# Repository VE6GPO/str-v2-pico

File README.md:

# Controlling NJW1194 pre-amp with RasPi Pico or Arduino Nano

### NJW1194 has:
- 4 stereo inputs
- SPI interface
- Volume control (separate L/R)
- Tone controls (Bass/Treble)

## Requirements:

### Audio inputs:
- AM Radio
- FM Radio
- IP Radio (Raspberry Pi as an internet radio stream receiver)
- External input (TV)

### MCU inputs - total 12 GPI:
- Power switch - 1 GPI
- Phono/AM/FM switch - 3 GPI
- Tape Select - 1 GPI
- Volume (rotary ctrl) - 2 GPI
- Mute - 1 GPI
- Bass/Treble/Balance - 3 ADC
- IR receiver - 1 GPI

### MCU outputs - total 9 GPO:
- Power relay - 1 GPO
- SPI (Data, Clock, ChipSelect) - 3 GPO
- RGB dial light (PWM) - 3 GPO
- Display I2C - 2 GPO

MCU needs 21 GPIO lines in total, plus maybe another 2 to "talk" to Raspberry Pi ...

### TODO:

- Utilize rotary encoder w. push button for Volume/Mute control
- Use existing pots fed to ADC for controlling Tone + Balance

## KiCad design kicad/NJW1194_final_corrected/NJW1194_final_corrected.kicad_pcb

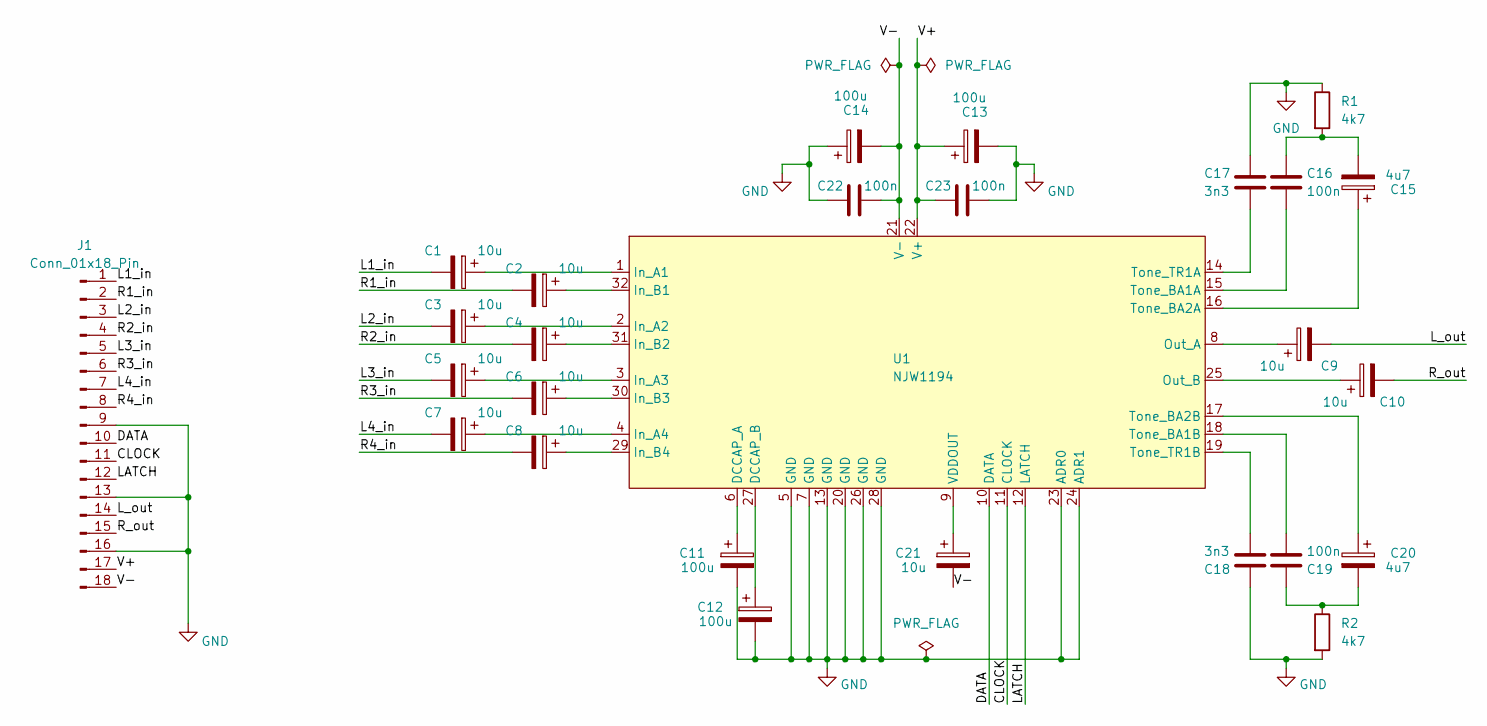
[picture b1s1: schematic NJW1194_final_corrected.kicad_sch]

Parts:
C1, C2, C3, C4, C5, C6, C7, C8, C9, C10, C21: 10u; CP_Elec_4x5.7
C11, C12, C13, C14: 100u; CP_Elec_6.3x7.7
C15, C20: 4u7; CP_Elec_4x5.7
C16, C19, C22, C23: 100n; C_0805_2012Metric_Pad1.18x1.45mm_HandSolder
C17, C18: 3n3; C_0805_2012Metric_Pad1.18x1.45mm_HandSolder
J1: Conn_01x18_Pin; PinHeader_1x18_P2.54mm_Vertical
R1, R2: 4k7; R_1206_3216Metric_Pad1.30x1.75mm_HandSolder
U1: NJW1194; TSSOP-32_6.1x11mm_P0.65mm

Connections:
/CLOCK: J1.11, U1.11 (CLOCK)
/DATA: J1.10, U1.10 (DATA)
/L1_in: C1.2, J1.1
/L2_in: C3.2, J1.3
/L3_in: C5.2, J1.5
/L4_in: C7.2, J1.7
/LATCH: J1.12, U1.12 (LATCH)
/L_out: C9.2, J1.14
/R1_in: C2.2, J1.2
/R2_in: C4.2, J1.4
/R3_in: C6.2, J1.6
/R4_in: C8.2, J1.8
/R_out: C10.2, J1.15
/V+: C13.1, C23.2, J1.17, U1.22 (V+)
/V-: C14.2, C21.2, C22.1, J1.18, U1.21 (V-)
GND: C11.2, C12.2, C13.2, C14.1, C17.1, C18.1, C22.2, C23.1, J1.9, J1.13, J1.16, R1.1, R2.2, U1.5 (GND), U1.7 (GND), U1.13 (GND), U1.20 (GND), U1.23 (ADR0), U1.24 (ADR1), U1.26 (GND), U1.28 (GND)
unnamed: C15.2, C16.1, R1.2
unnamed: C19.1, C20.2, R2.1
unnamed: C11.1, U1.6 (DCCAP_A)
unnamed: C12.1, U1.27 (DCCAP_B)
unnamed: C1.1, U1.1 (In_A1)
unnamed: C3.1, U1.2 (In_A2)
unnamed: C5.1, U1.3 (In_A3)
unnamed: C7.1, U1.4 (In_A4)
unnamed: C2.1, U1.32 (In_B1)
unnamed: C4.1, U1.31 (In_B2)
unnamed: C6.1, U1.30 (In_B3)
unnamed: C8.1, U1.29 (In_B4)
unnamed: C9.1, U1.8 (Out_A)
unnamed: C10.1, U1.25 (Out_B)
unnamed: C16.2, U1.15 (Tone_BA1A)
unnamed: C19.2, U1.18 (Tone_BA1B)
unnamed: C15.1, U1.16 (Tone_BA2A)
unnamed: C20.1, U1.17 (Tone_BA2B)
unnamed: C17.2, U1.14 (Tone_TR1A)
unnamed: C18.2, U1.19 (Tone_TR1B)
unnamed: C21.1, U1.9 (VDDOUT)

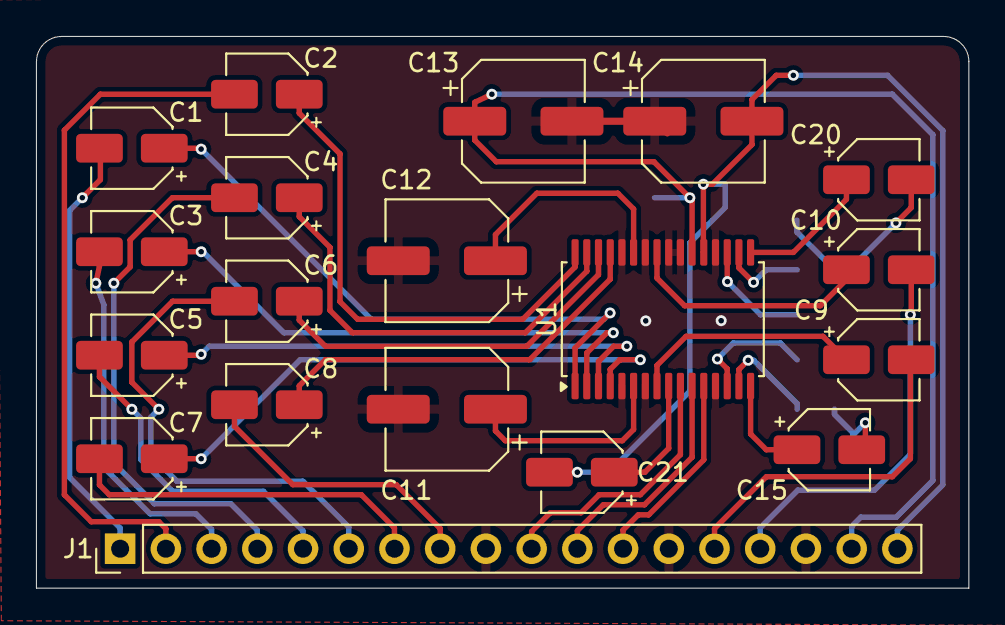
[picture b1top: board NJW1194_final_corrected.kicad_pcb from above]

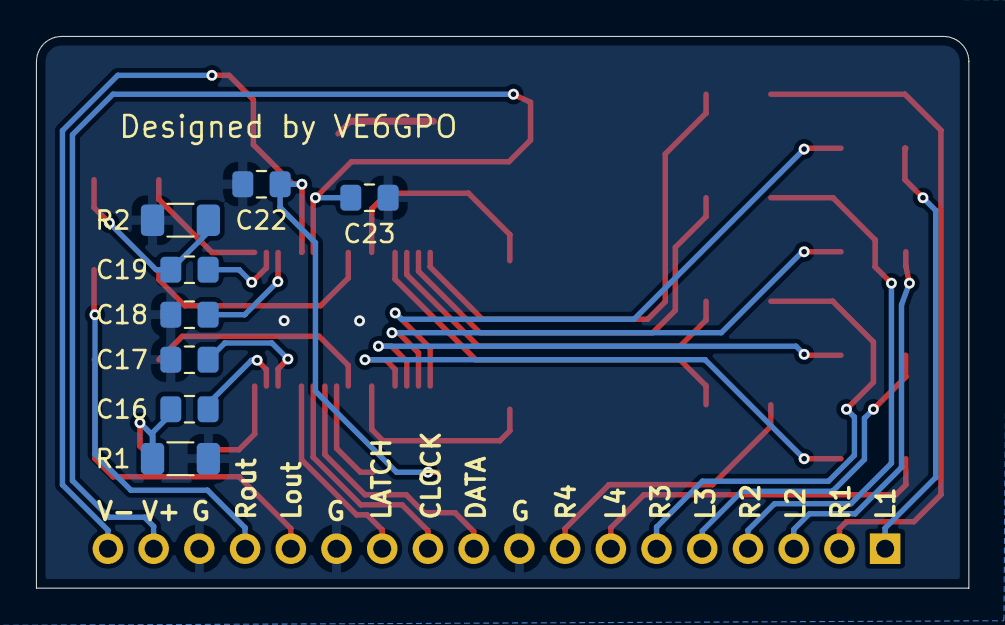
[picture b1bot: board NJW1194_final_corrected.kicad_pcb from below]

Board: 2 copper layers, 51.8 x 30.6 mm, 27 parts (8 on the bottom side), 37 nets.

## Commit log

2024-04-04 adds requirement line
2024-04-17 create docs and reorganize
2024-04-17 minor corrections
2024-04-18 reordering README
2024-04-18 adds kicad folder and NJW1194 project
2024-05-06 minor edits, articles
2024-05-06 corrects major mistake on the PCB, wrong IC footprint
2024-05-07 creates 'code' folder and adds NJW1194 library
2024-05-07 fix minor formatting
2024-05-07 adds LICENSE file and an example
2024-05-07 minor tweaks of NJW1194.h
2024-05-08 adds NJW1194-eeprom.ino file
2024-05-08 adds gitignore
